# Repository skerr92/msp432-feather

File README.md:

# msp432-feather

Welcome to the public repository for my MSP432P401R feather board design. There are just a few things that should be considered when working with this design. 

<image src="images/Screen Shot 2020-07-28 at 7.55.07 PM.png">
  
# Update (07-28-2020): Fixed issues with bad footprint for FT232RL chip

There was a connection and foodprint issue with the FT232RL chip which need to be replaced. That is reflected in the current board and schematic files.

In addition to this, 4 JTAG header pins are also added to allow programming from a MSP432P401R development board.

# Update (07-16-2020)

The schematic and board files were fixed related to the floating TEST pin on the FT232RL IC.

# Update (07-11-2020): If you choose to manufacture the current board uploaded read this first (fixed):

The old schematic is working to be updated following an issue with the FT232RL USB to UART chip. This is easy to overcome when assembling the current board, simply bridge pins 25 and 26 on the board. This ensures that pin 25 (TEST) is tied to pin 26 (GND). According to the FT232R datasheet, the chip won't be recognized because the test pin is floating. This will be corrected in the next revision.

# Get started today

You can get started by ordering the board from OshPark --> <a href="https://oshpark.com/shared_projects/jjmrRj4x">MSP432 Boards on OshPark</a>

# 1

The design is open for revision. If you have experience with PCB design and would like to contribue, I encourage you to do so! Simply create a fork of the repository and you're good to go!

If you are new to PCB design and want to play around with the files, you can do that to! Just download autodesk eagle through autodesk fusion and you can get started.

# 2

The BOM and board files are included for convenience if you so chose to build out this board. I am in the midst of testing the current design so I haven't worked out all the flaws that might be associate with this PCB. 

I should be done with the first board by the end of August, and I'll update the board files, schematic, and the lot as necessary.

# final thoughts

This board is the second board I have been working on and adding the the open source community. With hard work, I hope that this board can be successfully submitted the the Open Hardware Association as a means to help others who want to develop with the MSP432, can do so with the additional support of the Adafruit feather wings and other add-on boards.

If you have any questions, you can open up an issue in the <a href="https://github.com/skerr92/msp432-feather/issues">Issues</a> tab of this repository!

Please check the <a href="https://github.com/skerr92/msp432-feather/tree/master/technical%20documentation">Technical Documentation</a> for additional resources for working with the MSP432P4xxx microcontroller.

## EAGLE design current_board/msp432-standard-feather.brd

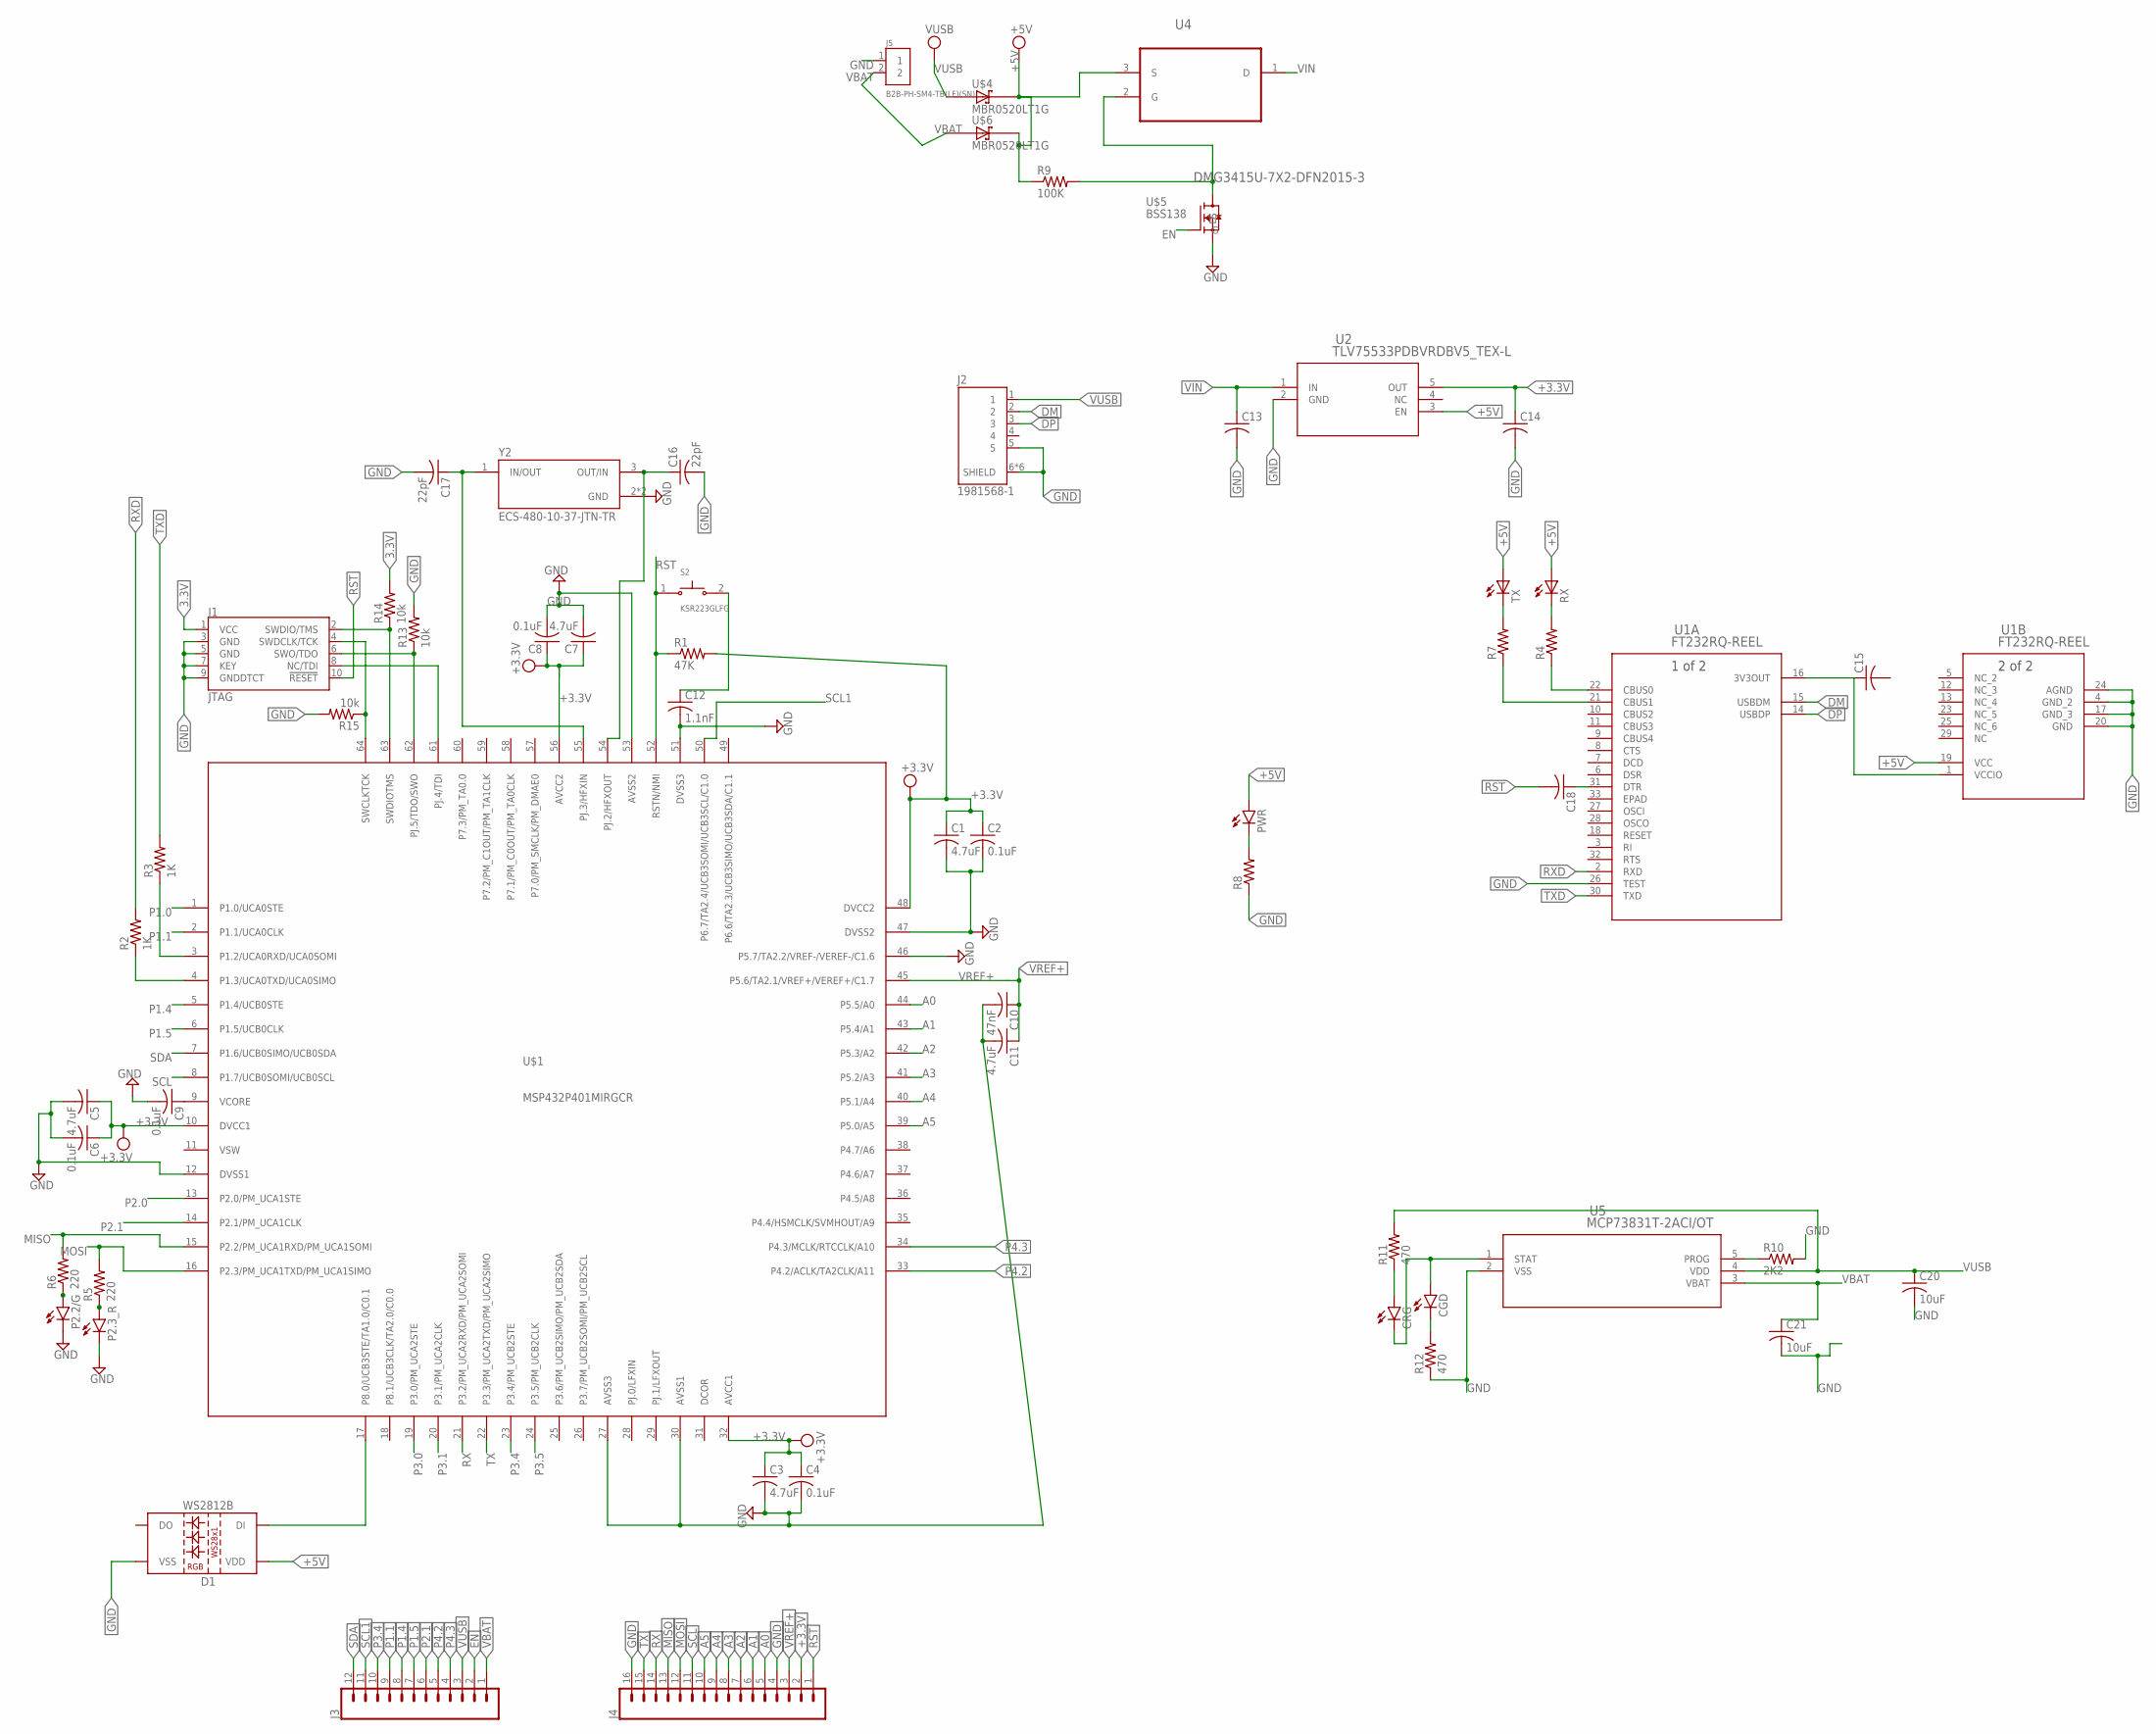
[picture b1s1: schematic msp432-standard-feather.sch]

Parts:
C1, C3, C5, C7, C11: 4.7uF; C0603
C2, C4, C6, C8, C9: 0.1uF; C0402
C10: 47nF; C0402
C12: 1.1nF; C0402
C13, C14, C15, C18: C-USC0402; C0402
C16, C17: 22pF; C0402
C20, C21: 10uF; C0603
CGD: LEDCHIP-LED0603; CHIP-LED0603
CRG: LEDCHIP-LED0603; CHIP-LED0603
D1: WS2812B
J1: JTAG; 2X5-SMD-1.27MM
J2: 1981568-1; TE_1981568-1
J3: CONN_12NO_SILK; 1X12_NO_SILK
J4: CONN_161X16_NO_SILK; 1X16_NO_SILK
J5: B2B-PH-SM4-TB(LF)(SN); JST_B2B-PH-SM4-TB(LF)(SN)
P2.2/G, P2.3_R: LEDCHIP-LED0603; CHIP-LED0603
PWR: LEDCHIP-LED0603; CHIP-LED0603
R1: 47K; R0402
R2, R3: 1K; R0402
R4, R7, R8: R-US_R0402; R0402
R5, R6: 220; R0402
R9: 100K; R0402
R10: 2K2; R0402
R11, R12: 470; R0402
R13, R14, R15: 10k; R0402
RX: LEDCHIP-LED0603; CHIP-LED0603
S2: KSR223GLFG; SW_KSR223GLFG
TX: LEDCHIP-LED0603; CHIP-LED0603
U1: FT232RQ-REEL; FT232RQ-REEL_FTD
U2: TLV75533PDBVRDBV5_TEX-L; DBV5_TEX-L
U4: DMG3415U-7X2-DFN2015-3; X2-DFN2015-3
U5: MCP73831T-2ACI/OT; SOT-23-5_MC
U$1: MSP432P401MIRGCR; MSP432_QFN_64
U$4, U$6: MBR0520LT1G; SOD3716X117(SOD-123)
U$5: BSS138
Y2: ECS-480-10-37-JTN-TR; XTAL_ECS-480-10-37-JTN-TR

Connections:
3.3V: J1.1 (VCC), R14.2
+3.3V: C1.1, C2.1, C3.1, C4.1, C5.1, C6.1, C7.1, C8.1, C14.1, J4.2, R1.2, U2.5 (OUT), U$1.10 (DVCC1), U$1.32 (AVCC1), U$1.48 (DVCC2), U$1.56 (AVCC2)
+5V: D1.1 (VDD), PWR.A, R9.1, RX.A, TX.A, U1.19 (VCC), U2.3 (EN), U4.3 (S), U$4.1 (C), U$6.1 (C)
A0: J4.5, U$1.44 (P5.5/A0)
A1: J4.6, U$1.43 (P5.4/A1)
A2: J4.7, U$1.42 (P5.3/A2)
A3: J4.8, U$1.41 (P5.2/A3)
A4: J4.9, U$1.40 (P5.1/A4)
A5: J4.10, U$1.39 (P5.0/A5)
DM: J2.2, U1.15 (USBDM)
DP: J2.3, U1.14 (USBDP)
EN: J3.2, U$5.G
GND: C1.2, C2.2, C3.2, C4.2, C5.2, C6.2, C7.2, C8.2, C9.2, C10.2, C11.2, C12.2, C13.2, C14.2, C16.2, C17.2, C20.2, C21.2, D1.3 (VSS), J1.3 (GND), J1.5 (GND), J1.7 (KEY), J1.9 (GNDDTCT), J2.5, J2.6 (SHIELD), J2.7 (SHIELD), J2.8 (SHIELD), J2.9 (SHIELD), J2.10 (SHIELD), J2.11 (SHIELD), J4.4, J4.16, J5.1, P2.2/G.C, P2.3_R.C, R8.1, R10.2, R12.1, R13.2, R15.2, U1.4 (GND_2), U1.17 (GND_3), U1.20 (GND), U1.24 (AGND), U1.26 (TEST), U2.2 (GND), U5.2 (VSS), U$1.12 (DVSS1), U$1.27 (AVSS3), U$1.30 (AVSS1), U$1.46 (P5.7/TA2.2/VREF-/VEREF-/C1.6), U$1.47 (DVSS2), U$1.51 (DVSS3), U$1.53 (AVSS2), U$5.S, Y2.2 (GND), Y2.4 (GND)
MISO: J4.13, R6.2, U$1.15 (P2.2/PM_UCA1RXD/PM_UCA1SOMI)
MOSI: J4.12, R5.2, U$1.16 (P2.3/PM_UCA1TXD/PM_UCA1SIMO)
unnamed: C9.1, U$1.9 (VCORE)
unnamed: R10.1, U5.5 (PROG)
unnamed: C15.1, U1.1 (VCCIO), U1.16 (3V3OUT)
unnamed: C18.1, U1.31 (DTR)
unnamed: R7.1, U1.21 (CBUS1)
unnamed: R4.1, U1.22 (CBUS0)
unnamed: R4.2, RX.C
unnamed: R7.2, TX.C
unnamed: J1.4 (SWDCLK/TCK), R15.1, U$1.64 (SWCLKTCK)
unnamed: C12.1, S2.2
unnamed: J1.2 (SWDIO/TMS), R14.1, U$1.63 (SWDIOTMS)
unnamed: PWR.C, R8.2
unnamed: P2.2/G.A, R6.1
unnamed: R2.1, U$1.4 (P1.3/UCA0TXD/UCA0SIMO)
unnamed: R3.1, U$1.3 (P1.2/UCA0RXD/UCA0SOMI)
unnamed: J1.6 (SWO/TDO), R13.1, U$1.62 (PJ.5/TDO/SWO)
unnamed: R9.2, U4.2 (G), U$5.D
unnamed: CGD.A, CRG.C, U5.1 (STAT)
unnamed: J1.8 (NC/TDI), U$1.61 (PJ.4/TDI)
unnamed: D1.4 (DI), U$1.17 (P8.0/UCB3STE/TA1.0/C0.1)
unnamed: CGD.C, R12.2
unnamed: CRG.A, R11.1
unnamed: P2.3_R.A, R5.1
unnamed: C16.1, U$1.54 (PJ.2/HFXOUT), Y2.3 (OUT/IN)
unnamed: C17.1, U$1.55 (PJ.3/HFXIN), Y2.1 (IN/OUT)
P1.0: U$1.1 (P1.0/UCA0STE)
P1.1: J3.9, U$1.2 (P1.1/UCA0CLK)
P1.4: J3.8, U$1.5 (P1.4/UCB0STE)
P1.5: J3.7, U$1.6 (P1.5/UCB0CLK)
P2.0: U$1.13 (P2.0/PM_UCA1STE)
P2.1: J3.6, U$1.14 (P2.1/PM_UCA1CLK)
P3.0: U$1.19 (P3.0/PM_UCA2STE)
P3.1: U$1.20 (P3.1/PM_UCA2CLK)
P3.4: J3.10, U$1.23 (P3.4/PM_UCB2STE)
P3.5: U$1.24 (P3.5/PM_UCB2CLK)
P4.2: J3.5, U$1.33 (P4.2/ACLK/TA2CLK/A11)
P4.3: J3.4, U$1.34 (P4.3/MCLK/RTCCLK/A10)
RST: C18.2, J1.10 (!RESET), J4.1, R1.1, S2.1, U$1.52 (RSTN/NMI)
RX: J4.14, U$1.21 (P3.2/PM_UCA2RXD/PM_UCA2SOMI)
RXD: R2.2, U1.2 (RXD)
SCL: J4.11, U$1.8 (P1.7/UCB0SOMI/UCB0SCL)
SCL1: J3.11, U$1.50 (P6.7/TA2.4/UCB3SOMI/UCB3SCL/C1.0)
SDA: J3.12, U$1.7 (P1.6/UCB0SIMO/UCB0SDA)
TX: J4.15, U$1.22 (P3.3/PM_UCA2TXD/PM_UCA2SIMO)
TXD: R3.2, U1.30 (TXD)
VBAT: C21.1, J3.1, J5.2, U5.3 (VBAT), U$6.2 (A)
VIN: C13.1, U2.1 (IN), U4.1 (D)
VREF+: C10.1, C11.1, J4.3, U$1.45 (P5.6/TA2.1/VREF+/VEREF+/C1.7)
VUSB: C20.1, J2.1, J3.3, R11.2, U5.4 (VDD), U$4.2 (A)

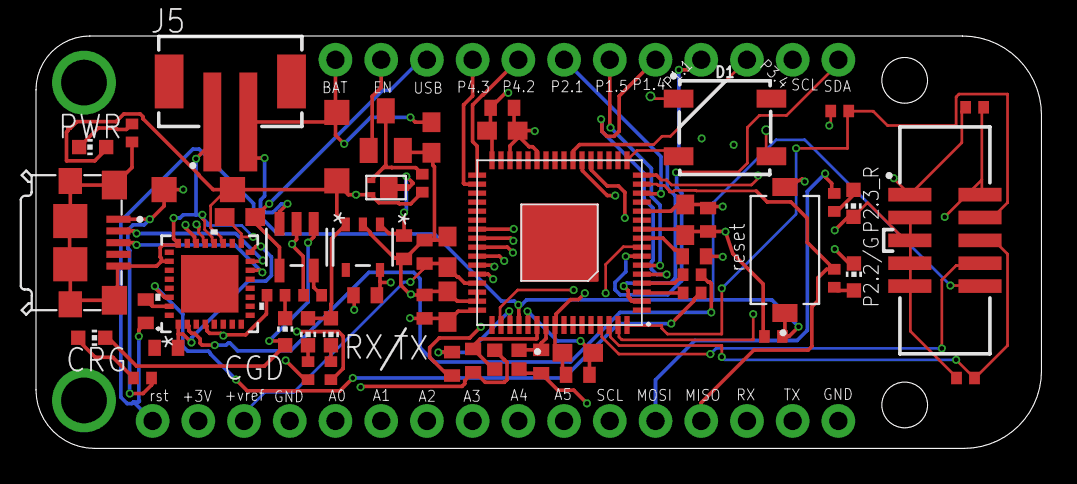
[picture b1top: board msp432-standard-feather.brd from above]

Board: 4 copper layers, 55.9 x 22.9 mm, 58 parts (0 on the bottom side), 59 nets.

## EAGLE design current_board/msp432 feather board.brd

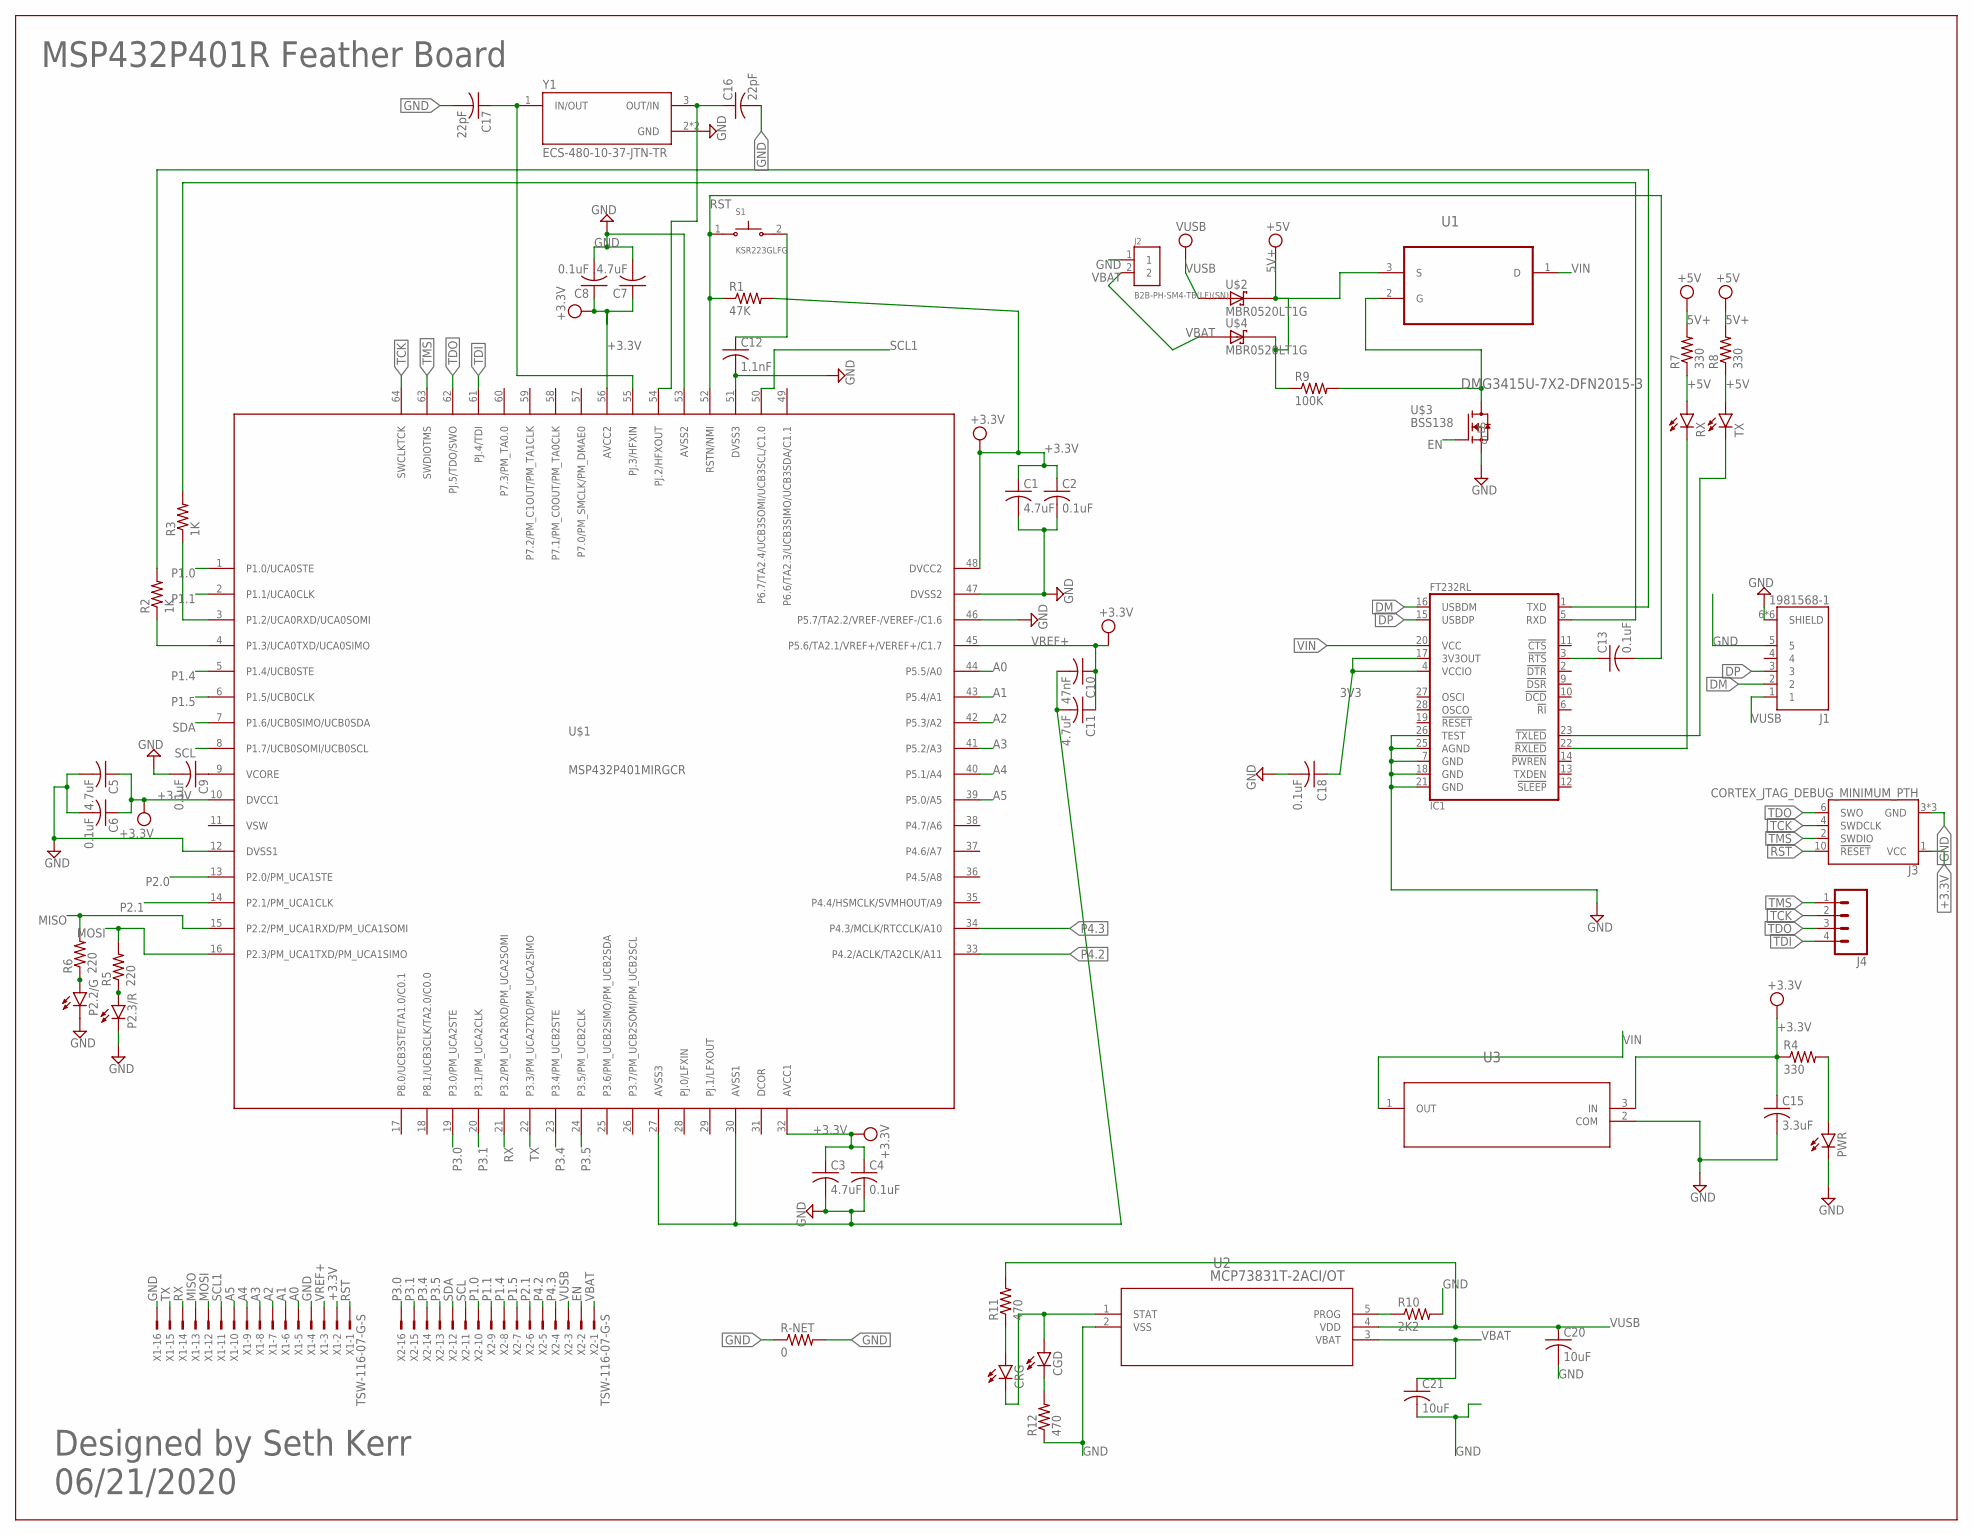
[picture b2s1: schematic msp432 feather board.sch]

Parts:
C1, C3, C5, C7, C11: 4.7uF; C0603
C2, C4, C6, C8, C9, C18: 0.1uF; C0402
C10: 47nF; C0402
C12: 1.1nF; C0402
C13: 0.1uF; C0603
C15: 3.3uF; C0603
C16, C17: 22pF; C0402
C20, C21: 10uF; C0603
CGD: LEDCHIP-LED0603; CHIP-LED0603
CRG: LEDCHIP-LED0603; CHIP-LED0603
IC1: FT232RL; SSOP28-LD
J1: 1981568-1; TE_1981568-1
J2: B2B-PH-SM4-TB(LF)(SN); JST_B2B-PH-SM4-TB(LF)(SN)
J3: CORTEX_JTAG_DEBUG_MINIMUM_PTH; 2X5-PTH-1.27MM
J4: CONN_041X04_NO_SILK; 1X04_NO_SILK
P2.2/G, P2.3/R: LEDCHIP-LED0603; CHIP-LED0603
PWR: LEDCHIP-LED0603; CHIP-LED0603
R1: 47K; R0402
R2, R3: 1K; R0402
R4, R7, R8: 330; R0402
R5, R6: 220; R0402
R9: 100K; R0402
R10: 2K2; R0402
R11, R12: 470; R0402
R-NET: 0; R0805
RX: LEDCHIP-LED0603; CHIP-LED0603
S1: KSR223GLFG; SW_KSR223GLFG
TX: LEDCHIP-LED0603; CHIP-LED0603
U1: DMG3415U-7X2-DFN2015-3; X2-DFN2015-3
U2: MCP73831T-2ACI/OT; SOT-23-5_MC
U3: UA78M05CDCYR; DCY4
U$1: MSP432P401MIRGCR; MSP432_QFN_64
U$2, U$4: MBR0520LT1G; SOD3716X117(SOD-123)
U$3: BSS138
X1, X2: TSW-116-07-G-S; TSW-116-XX-G-S
Y1: ECS-480-10-37-JTN-TR; XTAL_ECS-480-10-37-JTN-TR

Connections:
3V3: C18.1, IC1.4 (VCCIO), IC1.17 (3V3OUT)
5V+: R7.2, R8.2, R9.1, U1.3 (S), U$2.1 (C), U$4.1 (C)
+3.3V: C1.1, C2.1, C3.1, C4.1, C5.1, C6.1, C7.1, C8.1, C15.1, J3.1 (VCC), R1.2, R4.1, U3.3 (IN), U$1.10 (DVCC1), U$1.32 (AVCC1), U$1.48 (DVCC2), U$1.56 (AVCC2), X1.2
+5V: R7.1, R8.1, RX.A, TX.A
A0: U$1.44 (P5.5/A0), X1.5
A1: U$1.43 (P5.4/A1), X1.6
A2: U$1.42 (P5.3/A2), X1.7
A3: U$1.41 (P5.2/A3), X1.8
A4: U$1.40 (P5.1/A4), X1.9
A5: U$1.39 (P5.0/A5), X1.10
DM: IC1.16 (USBDM), J1.2
DP: IC1.15 (USBDP), J1.3
EN: U$3.G, X2.2
GND: C1.2, C2.2, C3.2, C4.2, C5.2, C6.2, C7.2, C8.2, C9.2, C10.2, C11.2, C12.2, C15.2, C16.2, C17.2, C18.2, C20.2, C21.2, IC1.7 (GND), IC1.18 (GND), IC1.21 (GND), IC1.25 (AGND), IC1.26 (TEST), J1.5, J1.6 (SHIELD), J1.7 (SHIELD), J1.8 (SHIELD), J1.9 (SHIELD), J1.10 (SHIELD), J1.11 (SHIELD), J2.1, J3.3 (GND), J3.5 (GND), J3.9 (GND), P2.2/G.C, P2.3/R.C, PWR.C, R10.2, R12.1, R-NET.1, R-NET.2, U2.2 (VSS), U3.2 (COM), U$1.12 (DVSS1), U$1.27 (AVSS3), U$1.30 (AVSS1), U$1.46 (P5.7/TA2.2/VREF-/VEREF-/C1.6), U$1.47 (DVSS2), U$1.51 (DVSS3), U$1.53 (AVSS2), U$3.S, X1.4, X1.16, Y1.2 (GND), Y1.4 (GND)
MISO: R6.2, U$1.15 (P2.2/PM_UCA1RXD/PM_UCA1SOMI), X1.13
MOSI: R5.2, U$1.16 (P2.3/PM_UCA1TXD/PM_UCA1SIMO), X1.12
unnamed: C9.1, U$1.9 (VCORE)
unnamed: R10.1, U2.5 (PROG)
unnamed: C13.1, IC1.3 (!RTS)
unnamed: IC1.5 (RXD), R3.2
unnamed: IC1.1 (TXD), R2.2
unnamed: C12.1, S1.2
unnamed: IC1.22 (!RXLED), RX.C
unnamed: IC1.23 (!TXLED), TX.C
unnamed: P2.2/G.A, R6.1
unnamed: R2.1, U$1.4 (P1.3/UCA0TXD/UCA0SIMO)
unnamed: R3.1, U$1.3 (P1.2/UCA0RXD/UCA0SOMI)
unnamed: R9.2, U1.2 (G), U$3.D
unnamed: CGD.A, CRG.C, U2.1 (STAT)
unnamed: CGD.C, R12.2
unnamed: CRG.A, R11.1
unnamed: PWR.A, R4.2
unnamed: P2.3/R.A, R5.1
unnamed: C16.1, U$1.54 (PJ.2/HFXOUT), Y1.3 (OUT/IN)
unnamed: C17.1, U$1.55 (PJ.3/HFXIN), Y1.1 (IN/OUT)
P1.0: U$1.1 (P1.0/UCA0STE), X2.10
P1.1: U$1.2 (P1.1/UCA0CLK), X2.9
P1.4: U$1.5 (P1.4/UCB0STE), X2.8
P1.5: U$1.6 (P1.5/UCB0CLK), X2.7
P2.0: U$1.13 (P2.0/PM_UCA1STE)
P2.1: U$1.14 (P2.1/PM_UCA1CLK), X2.6
P3.0: U$1.19 (P3.0/PM_UCA2STE), X2.16
P3.1: U$1.20 (P3.1/PM_UCA2CLK), X2.15
P3.4: U$1.23 (P3.4/PM_UCB2STE), X2.14
P3.5: U$1.24 (P3.5/PM_UCB2CLK), X2.13
P4.2: U$1.33 (P4.2/ACLK/TA2CLK/A11), X2.5
P4.3: U$1.34 (P4.3/MCLK/RTCCLK/A10), X2.4
RST: C13.2, J3.10 (!RESET), R1.1, S1.1, U$1.52 (RSTN/NMI), X1.1
RX: U$1.21 (P3.2/PM_UCA2RXD/PM_UCA2SOMI), X1.14
SCL: U$1.8 (P1.7/UCB0SOMI/UCB0SCL), X2.11
SCL1: U$1.50 (P6.7/TA2.4/UCB3SOMI/UCB3SCL/C1.0), X1.11
SDA: U$1.7 (P1.6/UCB0SIMO/UCB0SDA), X2.12
TCK: J3.4 (SWDCLK), J4.2, U$1.64 (SWCLKTCK)
TDI: J4.4, U$1.61 (PJ.4/TDI)
TDO: J3.6 (SWO), J4.3, U$1.62 (PJ.5/TDO/SWO)
TMS: J3.2 (SWDIO), J4.1, U$1.63 (SWDIOTMS)
TX: U$1.22 (P3.3/PM_UCA2TXD/PM_UCA2SIMO), X1.15
VBAT: C21.1, J2.2, U2.3 (VBAT), U$4.2 (A), X2.1
VIN: IC1.20 (VCC), U1.1 (D), U3.1 (OUT)
VREF+: C10.1, C11.1, U$1.45 (P5.6/TA2.1/VREF+/VEREF+/C1.7), X1.3
VUSB: C20.1, J1.1, R11.2, U2.4 (VDD), U$2.2 (A), X2.3

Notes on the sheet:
Designed by Seth Kerr 06/21/2020
MSP432P401R Feather Board

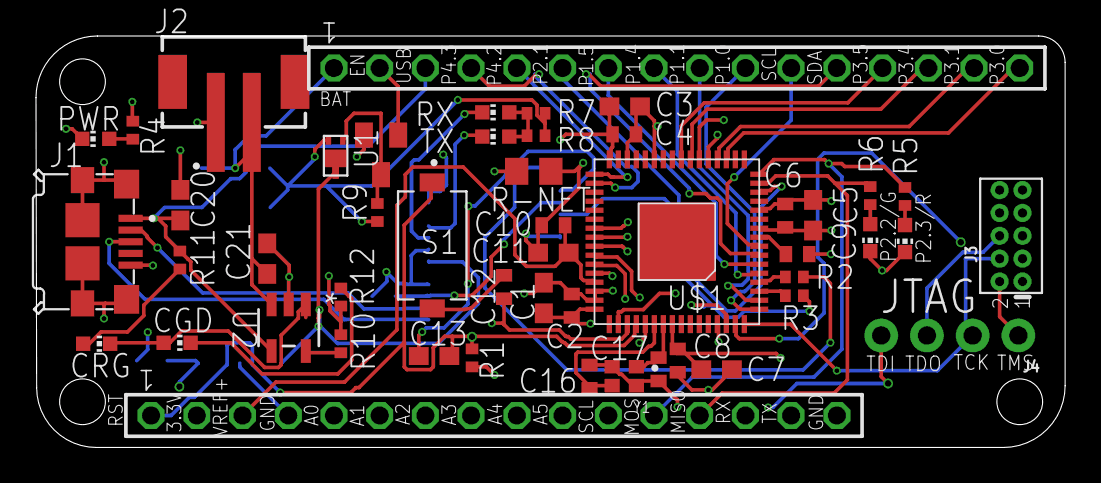
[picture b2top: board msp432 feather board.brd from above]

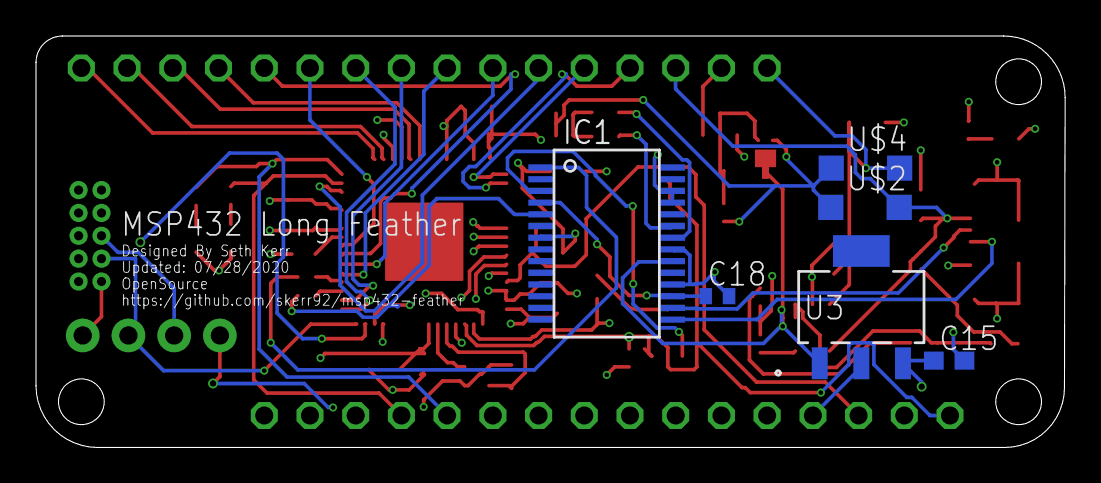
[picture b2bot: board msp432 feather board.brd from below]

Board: 4 copper layers, 57.2 x 22.9 mm, 55 parts (6 on the bottom side), 60 nets.

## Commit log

2020-06-21 Update README.md
    extending description and need to know.
2020-06-21 Add files via upload
    bill of materials that can be uploaded to DigiKey
2020-06-21 Update readme.md
    fixing link
2020-06-21 Update README.md
    adding final readme info
2020-06-21 Create LICENSE
2020-07-13 Update README.md
    updating information about TEST pin on FT232RL USB to UART chip on board.
2020-07-16 updated board file
    Fixed issue with floating TEST pin on FT232RL IC
2020-07-16 updating schematic
    Fixed issue with floating TEST pin on FT232RL IC
2020-07-16 updating readme
    updated readme to reflect changes to the board and schematic files
2020-07-16 providing oshpark link
    Adding the oshpark link to the readme
2020-07-28 Add files via upload
    fixing JTAG and adding ARM 10pin JTAG connector
2020-07-28 Add files via upload
    fixing JTAG stuff and adding 10 pin ARM JTAG to schematic and board.
2020-07-28 Add files via upload
    new image for readme
2020-07-29 Add files via upload
    wiring issues with the USB interface.
2020-07-29 Add files via upload
    fixed wiring issues on the schematic for the usb interface
2020-11-20 Add files via upload
    adding corrected feather
2020-11-20 Delete msp432 feather board.brd
    old design doesn't work
2020-11-20 Add files via upload
    updated schematic
2020-11-20 Delete msp432 feather board.sch
    removing old schematic

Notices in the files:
parts and their libraries:
SparkFun-Connectors: Licensing: Creative Commons ShareAlike 4.0 International - https://creativecommons.org/licenses/by-sa/4.0
COPYRIGHT: Copyright (C) 2018 Accelerated Designs. All rights reserved
